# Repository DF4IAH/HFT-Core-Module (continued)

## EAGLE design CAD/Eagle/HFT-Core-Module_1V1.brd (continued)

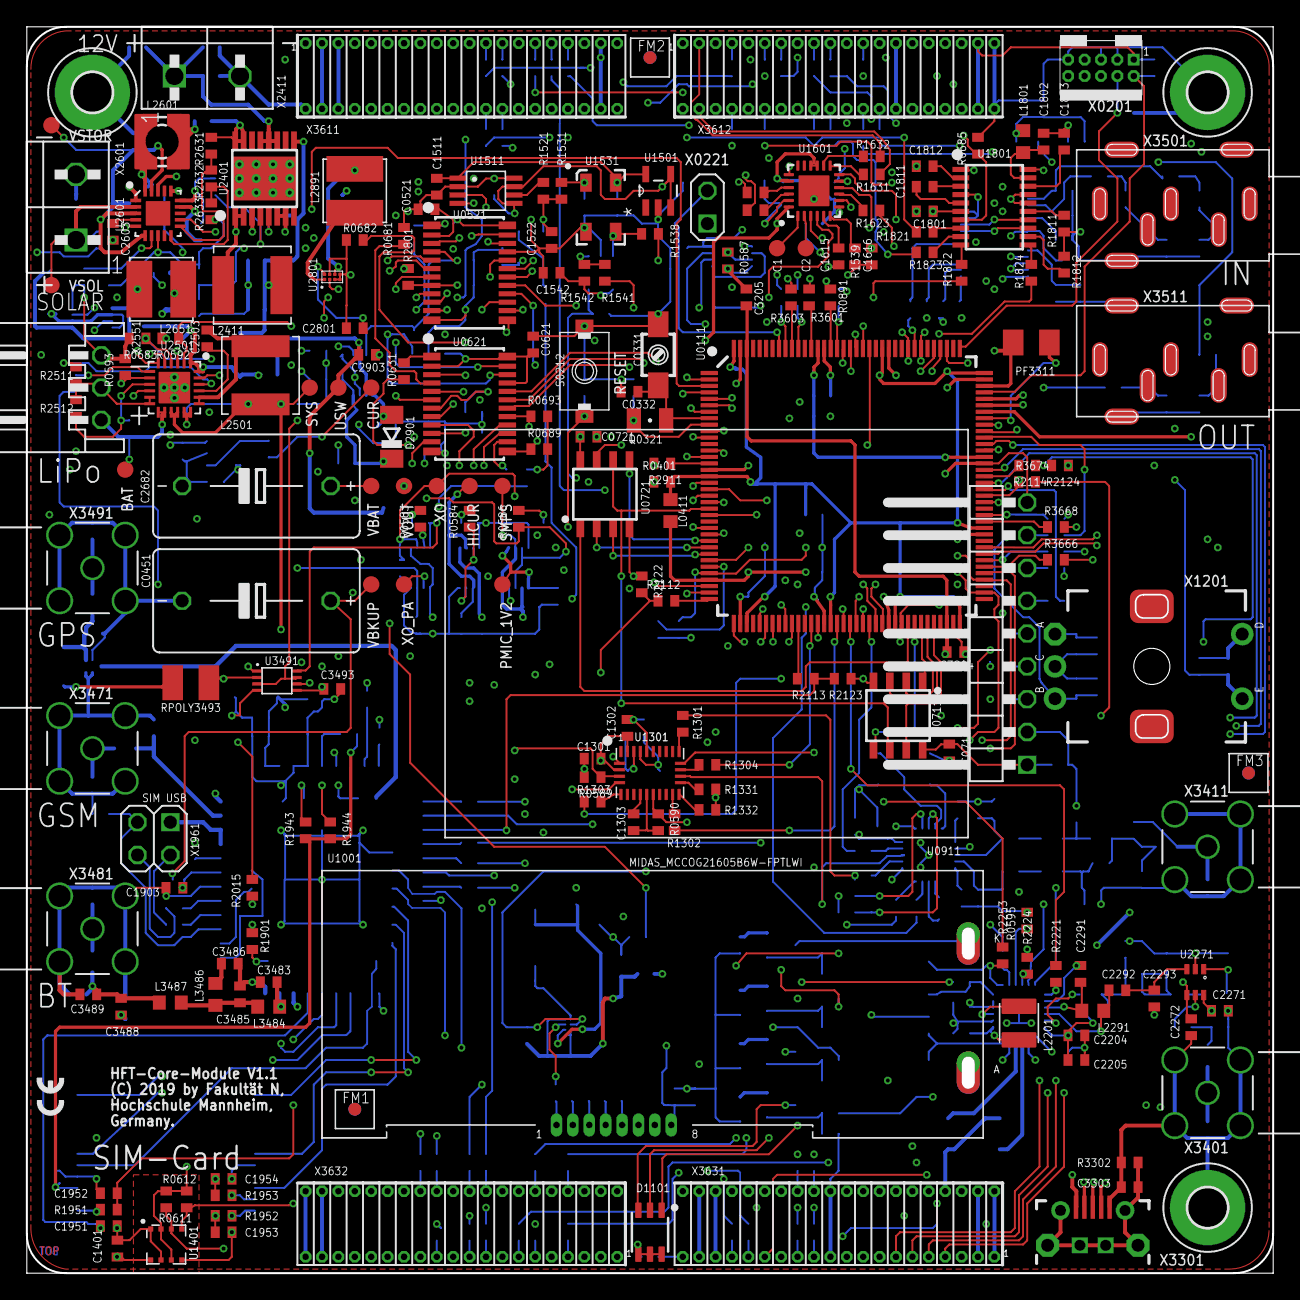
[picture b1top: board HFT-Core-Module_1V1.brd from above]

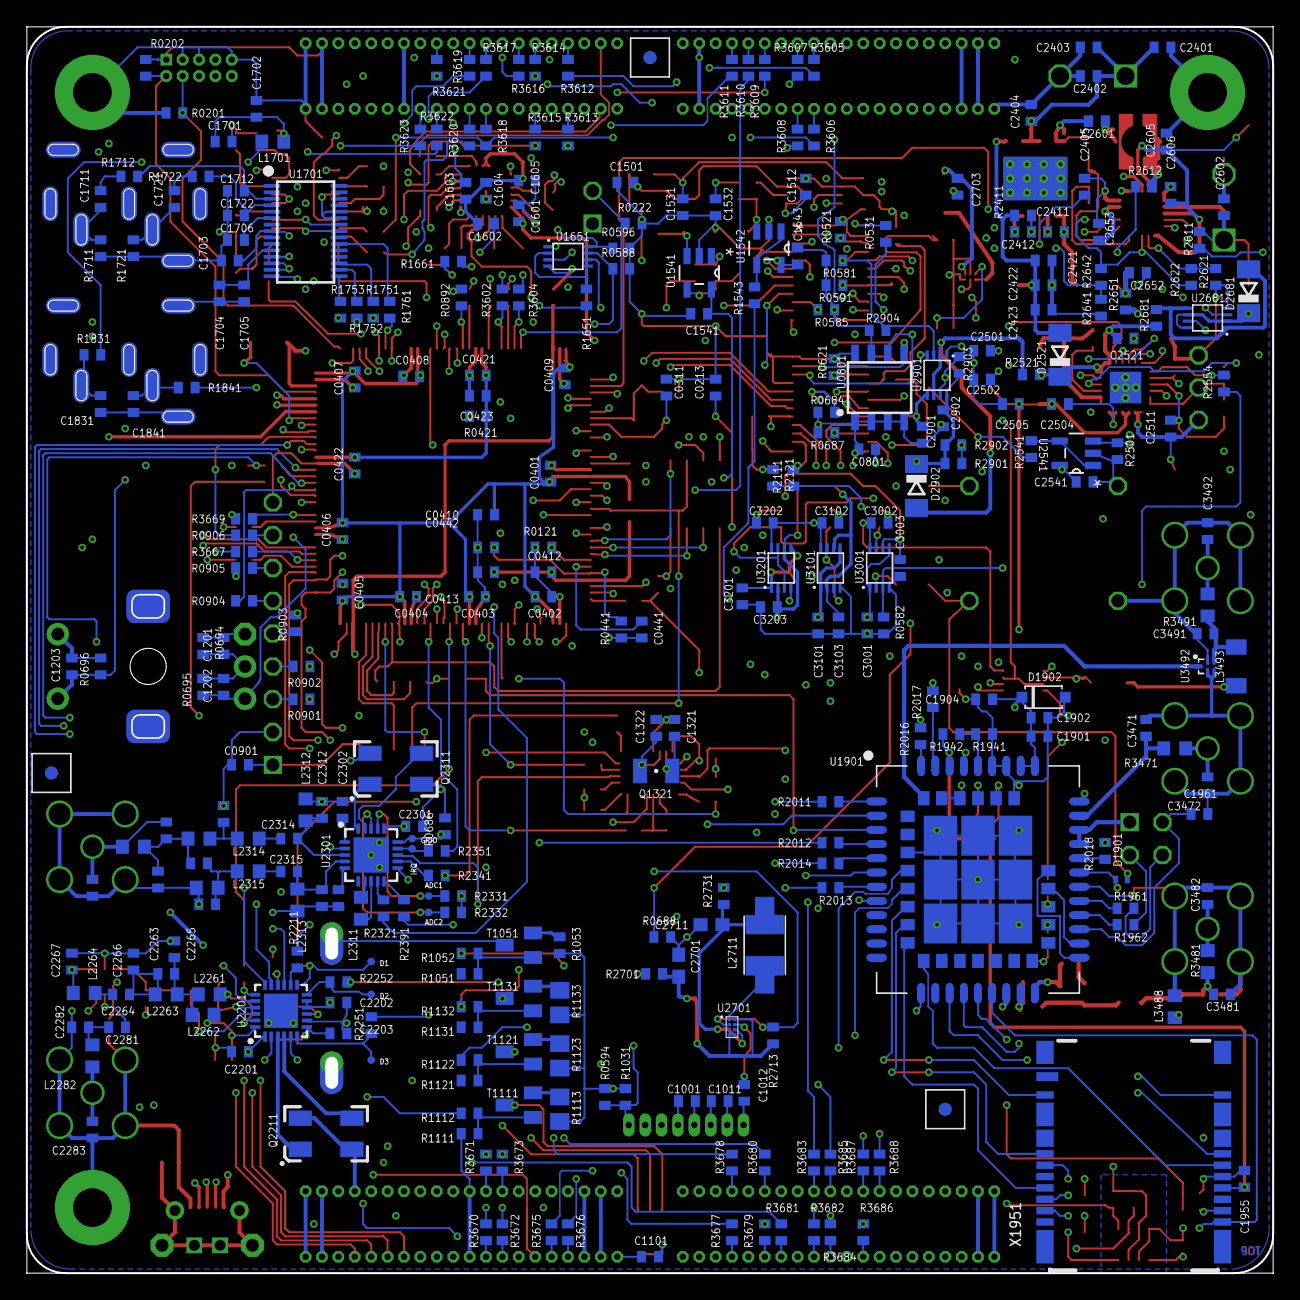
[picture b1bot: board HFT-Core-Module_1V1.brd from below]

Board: 6 copper layers, 96.5 x 96.5 mm, 518 parts (320 on the bottom side), 412 nets.

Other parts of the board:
FM1, FM2, FM3: FIDUCIAL_MARK_1MM

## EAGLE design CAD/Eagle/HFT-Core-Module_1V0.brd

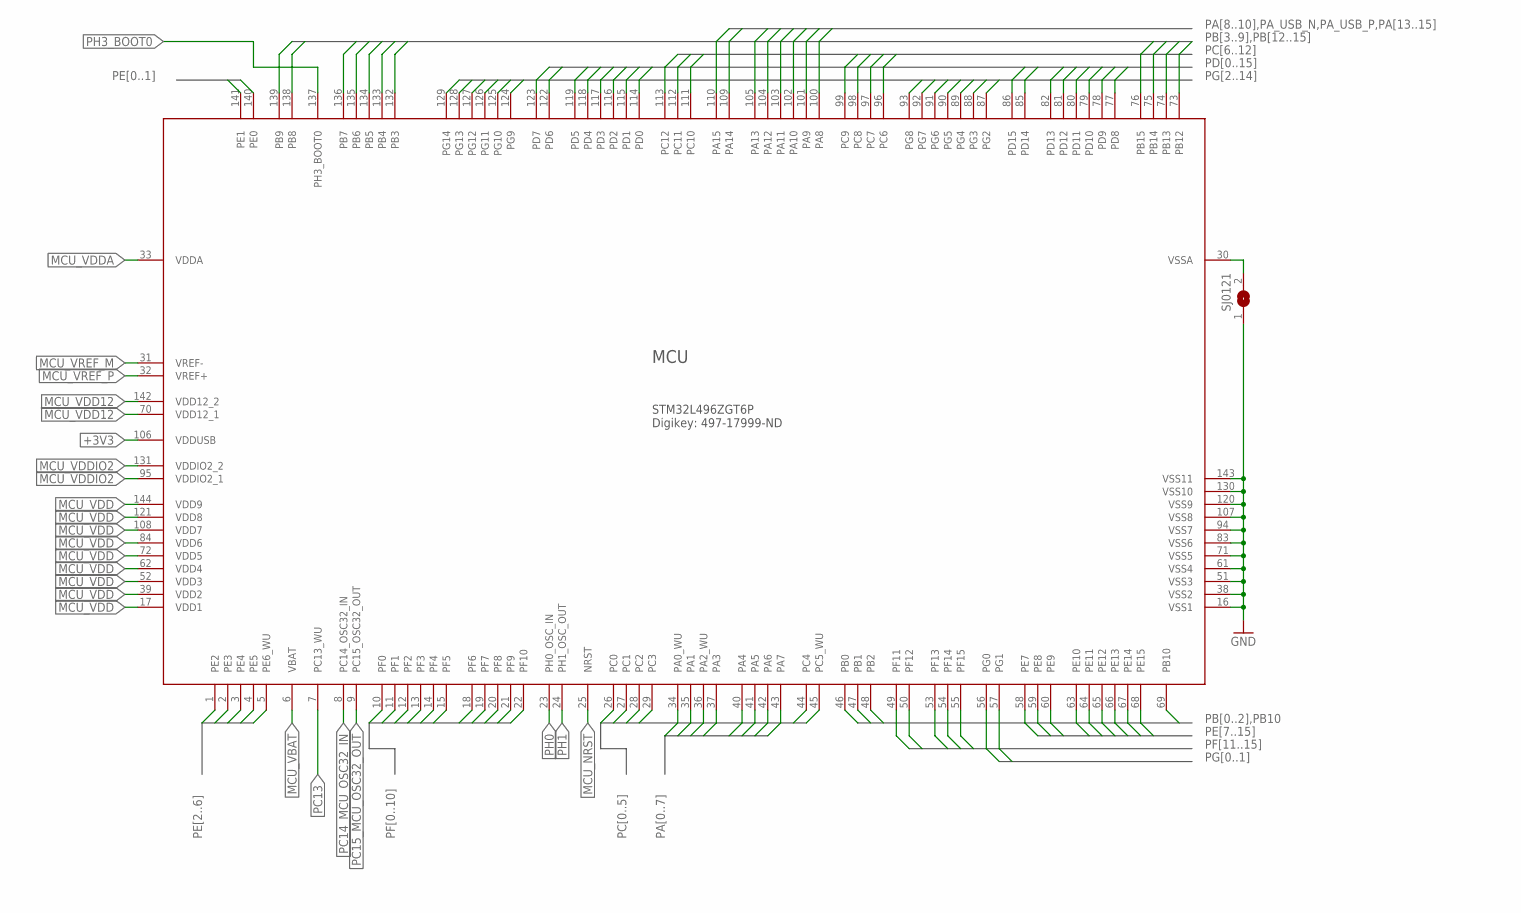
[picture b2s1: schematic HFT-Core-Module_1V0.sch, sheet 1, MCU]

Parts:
SJ0121: SJ
U0111: STM32L4Z_144PIN_SMPS; LQFP144

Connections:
+3V3: U0111.106 (VDDUSB); also elsewhere on the board
GND: SJ0121.1, U0111.16 (VSS1), U0111.38 (VSS2), U0111.51 (VSS3), U0111.61 (VSS4), U0111.71 (VSS5), U0111.83 (VSS6), U0111.94 (VSS7), U0111.107 (VSS8), U0111.120 (VSS9), U0111.130 (VSS10), U0111.143 (VSS11); also elsewhere on the board
MCU_NRST: U0111.25 (NRST); also elsewhere on the board
MCU_VBAT: U0111.6 (VBAT); also elsewhere on the board
MCU_VDD: U0111.17 (VDD1), U0111.39 (VDD2), U0111.52 (VDD3), U0111.62 (VDD4), U0111.72 (VDD5), U0111.84 (VDD6), U0111.108 (VDD7), U0111.121 (VDD8), U0111.144 (VDD9); also elsewhere on the board
MCU_VDD12: U0111.70 (VDD12_1), U0111.142 (VDD12_2); also elsewhere on the board
MCU_VDDA: U0111.33 (VDDA); also elsewhere on the board
MCU_VDDIO2: U0111.95 (VDDIO2_1), U0111.131 (VDDIO2_2); also elsewhere on the board
MCU_VREF_M: U0111.31 (VREF-); also elsewhere on the board
MCU_VREF_P: U0111.32 (VREF+); also elsewhere on the board
MCU_VSSA: SJ0121.2, U0111.30 (VSSA)
PA0: U0111.34 (PA0_WU); also elsewhere on the board
PA1: U0111.35 (PA1)
PA2: U0111.36 (PA2_WU); also elsewhere on the board
PA3: U0111.37 (PA3); also elsewhere on the board
PA4: U0111.40 (PA4)
PA5: U0111.41 (PA5)
PA6: U0111.42 (PA6); also elsewhere on the board
PA7: U0111.43 (PA7); also elsewhere on the board
PA8: U0111.100 (PA8); also elsewhere on the board
PA9: U0111.101 (PA9); also elsewhere on the board
PA10: U0111.102 (PA10); also elsewhere on the board
PA13: U0111.105 (PA13); also elsewhere on the board
PA14: U0111.109 (PA14); also elsewhere on the board
PA15: U0111.110 (PA15)
PA_USB_N: U0111.103 (PA11); also elsewhere on the board
PA_USB_P: U0111.104 (PA12); also elsewhere on the board
PB0: U0111.46 (PB0); also elsewhere on the board
PB1: U0111.47 (PB1); also elsewhere on the board
PB2: U0111.48 (PB2)
PB3: U0111.132 (PB3); also elsewhere on the board
PB4: U0111.133 (PB4)
PB5: U0111.134 (PB5); also elsewhere on the board
PB6: U0111.135 (PB6); also elsewhere on the board
PB7: U0111.136 (PB7); also elsewhere on the board
PB8: U0111.138 (PB8)
PB9: U0111.139 (PB9)
PB10: U0111.69 (PB10); also elsewhere on the board
PB12: U0111.73 (PB12); also elsewhere on the board
PB13: U0111.74 (PB13); also elsewhere on the board
PB14: U0111.75 (PB14); also elsewhere on the board
PB15: U0111.76 (PB15)
PC0: U0111.26 (PC0); also elsewhere on the board
PC1: U0111.27 (PC1); also elsewhere on the board
PC2: U0111.28 (PC2); also elsewhere on the board
PC3: U0111.29 (PC3); also elsewhere on the board
PC4: U0111.44 (PC4); also elsewhere on the board
PC5: U0111.45 (PC5_WU); also elsewhere on the board
PC6: U0111.96 (PC6); also elsewhere on the board
PC7: U0111.97 (PC7)
PC8: U0111.98 (PC8); also elsewhere on the board
PC9: U0111.99 (PC9); also elsewhere on the board
PC10: U0111.111 (PC10); also elsewhere on the board
PC11: U0111.112 (PC11); also elsewhere on the board
PC12: U0111.113 (PC12); also elsewhere on the board
PC13: U0111.7 (PC13_WU); also elsewhere on the board
PC14_MCU_OSC32_IN: U0111.8 (PC14_OSC32_IN); also elsewhere on the board
PC15_MCU_OSC32_OUT: U0111.9 (PC15_OSC32_OUT); also elsewhere on the board
PD0: U0111.114 (PD0); also elsewhere on the board
PD1: U0111.115 (PD1); also elsewhere on the board
PD2: U0111.116 (PD2); also elsewhere on the board
PD3: U0111.117 (PD3); also elsewhere on the board
PD4: U0111.118 (PD4); also elsewhere on the board
PD5: U0111.119 (PD5); also elsewhere on the board
PD6: U0111.122 (PD6); also elsewhere on the board
PD7: U0111.123 (PD7); also elsewhere on the board
PD8: U0111.77 (PD8); also elsewhere on the board
PD9: U0111.78 (PD9); also elsewhere on the board
PD10: U0111.79 (PD10); also elsewhere on the board
PD11: U0111.80 (PD11); also elsewhere on the board
PD12: U0111.81 (PD12); also elsewhere on the board
PD13: U0111.82 (PD13); also elsewhere on the board
PD14: U0111.85 (PD14); also elsewhere on the board
PD15: U0111.86 (PD15); also elsewhere on the board
PE0: U0111.140 (PE0); also elsewhere on the board
PE1: U0111.141 (PE1)
PE2: U0111.1 (PE2); also elsewhere on the board
PE3: U0111.2 (PE3); also elsewhere on the board
PE4: U0111.3 (PE4); also elsewhere on the board
PE5: U0111.4 (PE5); also elsewhere on the board
PE6: U0111.5 (PE6_WU)
PE7: U0111.58 (PE7); also elsewhere on the board
PE8: U0111.59 (PE8); also elsewhere on the board
PE9: U0111.60 (PE9); also elsewhere on the board
PE10: U0111.63 (PE10); also elsewhere on the board
PE11: U0111.64 (PE11); also elsewhere on the board
PE12: U0111.65 (PE12); also elsewhere on the board
PE13: U0111.66 (PE13); also elsewhere on the board
PE14: U0111.67 (PE14); also elsewhere on the board
PE15: U0111.68 (PE15); also elsewhere on the board
PF0: U0111.10 (PF0); also elsewhere on the board
PF1: U0111.11 (PF1); also elsewhere on the board
PF2: U0111.12 (PF2); also elsewhere on the board
PF3: U0111.13 (PF3); also elsewhere on the board
PF4: U0111.14 (PF4)
PF5: U0111.15 (PF5)
PF6: U0111.18 (PF6); also elsewhere on the board
PF7: U0111.19 (PF7); also elsewhere on the board
PF8: U0111.20 (PF8); also elsewhere on the board
PF9: U0111.21 (PF9); also elsewhere on the board
PF10: U0111.22 (PF10); also elsewhere on the board
PF11: U0111.49 (PF11)
PF12: U0111.50 (PF12); also elsewhere on the board
PF13: U0111.53 (PF13); also elsewhere on the board
PF14: U0111.54 (PF14); also elsewhere on the board
PF15: U0111.55 (PF15)
PG0: U0111.56 (PG0); also elsewhere on the board
PG1: U0111.57 (PG1); also elsewhere on the board
PG2: U0111.87 (PG2); also elsewhere on the board
PG3: U0111.88 (PG3); also elsewhere on the board
PG4: U0111.89 (PG4); also elsewhere on the board
PG5: U0111.90 (PG5)
PG6: U0111.91 (PG6)
PG7: U0111.92 (PG7); also elsewhere on the board
PG8: U0111.93 (PG8); also elsewhere on the board
PG9: U0111.124 (PG9); also elsewhere on the board
PG10: U0111.125 (PG10); also elsewhere on the board
PG11: U0111.126 (PG11); also elsewhere on the board
PG12: U0111.127 (PG12); also elsewhere on the board
PG13: U0111.128 (PG13); also elsewhere on the board
PG14: U0111.129 (PG14); also elsewhere on the board
PH0: U0111.23 (PH0_OSC_IN); also elsewhere on the board
PH1: U0111.24 (PH1_OSC_OUT)
PH3_BOOT0: U0111.137 (PH3_BOOT0); also elsewhere on the board

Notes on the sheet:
STM32L496ZGT6P Digikey: 497-17999-ND
MCU

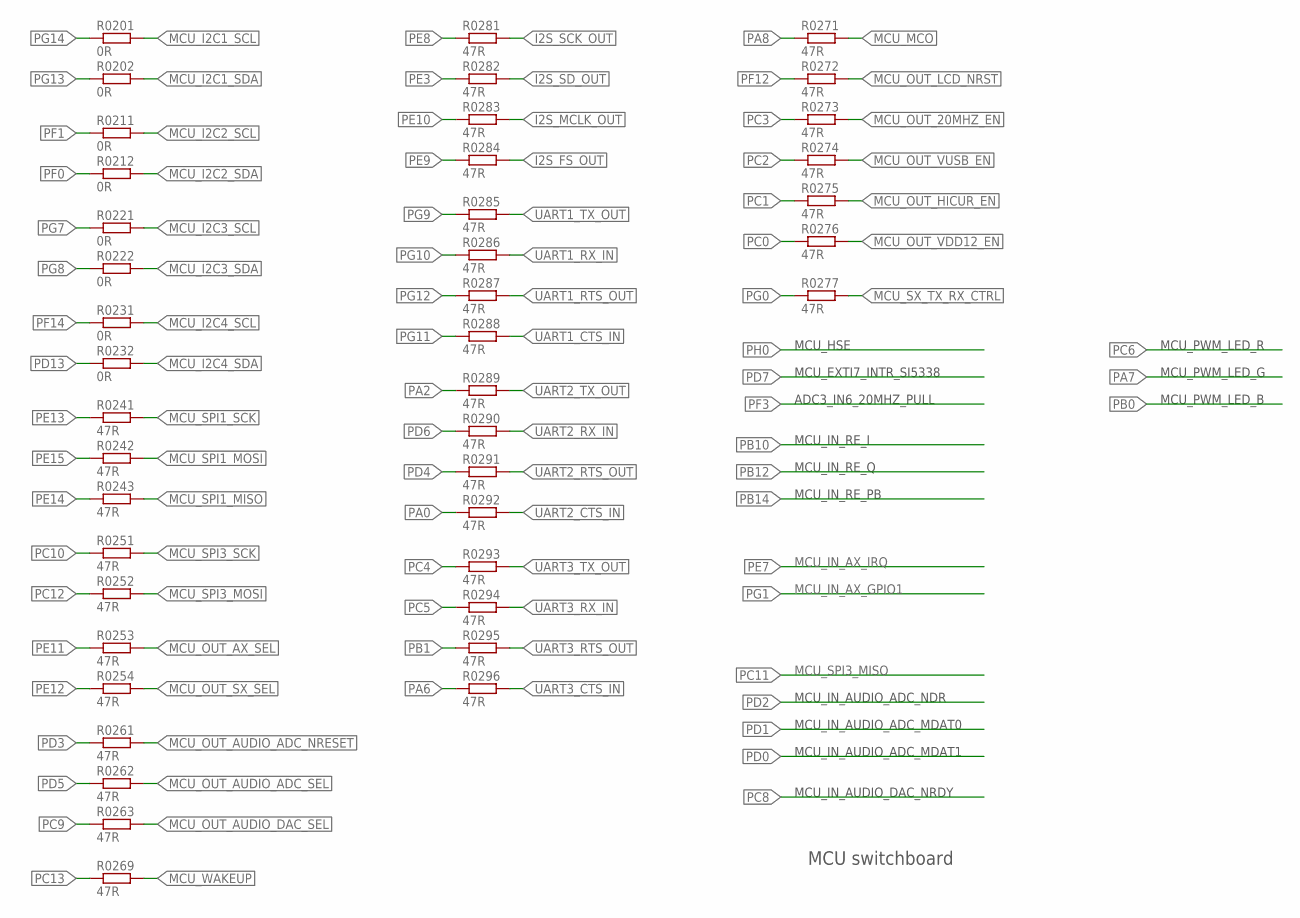
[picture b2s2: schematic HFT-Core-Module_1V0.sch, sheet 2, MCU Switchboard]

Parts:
R0201, R0202, R0211, R0212, R0221, R0222, R0231, R0232: 0R; R0603
R0241, R0242, R0243, R0251, R0252, R0253, R0254, R0261, R0262, R0263, R0269, R0271, R0272, R0273, R0274, R0275, R0276, R0277, R0281, R0282, R0283, R0284, R0285, R0286, R0287, R0288, R0289, R0290, R0291, R0292, R0293, R0294, R0295, R0296: 47R; R0603

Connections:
I2S_FS_OUT: R0284.2; also elsewhere on the board
I2S_MCLK_OUT: R0283.2; also elsewhere on the board
I2S_SCK_OUT: R0281.2; also elsewhere on the board
I2S_SD_OUT: R0282.2; also elsewhere on the board
MCU_I2C1_SCL: R0201.2; also elsewhere on the board
MCU_I2C1_SDA: R0202.2; also elsewhere on the board
MCU_I2C2_SCL: R0211.2; also elsewhere on the board
MCU_I2C2_SDA: R0212.2; also elsewhere on the board
MCU_I2C3_SCL: R0221.2; also elsewhere on the board
MCU_I2C3_SDA: R0222.2; also elsewhere on the board
MCU_I2C4_SCL: R0231.2; also elsewhere on the board
MCU_I2C4_SDA: R0232.2; also elsewhere on the board
MCU_MCO: R0271.2; also elsewhere on the board
MCU_OUT_20MHZ_EN: R0273.2; also elsewhere on the board
MCU_OUT_AUDIO_ADC_NRESET: R0261.2; also elsewhere on the board
MCU_OUT_AUDIO_ADC_SEL: R0262.2; also elsewhere on the board
MCU_OUT_AUDIO_DAC_SEL: R0263.2; also elsewhere on the board
MCU_OUT_AX_SEL: R0253.2; also elsewhere on the board
MCU_OUT_HICUR_EN: R0275.2; also elsewhere on the board
MCU_OUT_LCD_NRST: R0272.2; also elsewhere on the board
MCU_OUT_SX_SEL: R0254.2; also elsewhere on the board
MCU_OUT_VDD12_EN: R0276.2; also elsewhere on the board
MCU_OUT_VUSB_EN: R0274.2; also elsewhere on the board
MCU_SPI1_MISO: R0243.2; also elsewhere on the board
MCU_SPI1_MOSI: R0242.2; also elsewhere on the board
MCU_SPI1_SCK: R0241.2; also elsewhere on the board
MCU_SPI3_MOSI: R0252.2; also elsewhere on the board
MCU_SPI3_SCK: R0251.2; also elsewhere on the board
MCU_SX_TX_RX_CTRL: R0277.2; also elsewhere on the board
MCU_WAKEUP: R0269.2; also elsewhere on the board
PA0: R0292.1; also elsewhere on the board
PA2: R0289.1; also elsewhere on the board
PA6: R0296.1; also elsewhere on the board
PA8: R0271.1; also elsewhere on the board
PB1: R0295.1; also elsewhere on the board
PC0: R0276.1; also elsewhere on the board
PC1: R0275.1; also elsewhere on the board
PC2: R0274.1; also elsewhere on the board
PC3: R0273.1; also elsewhere on the board
PC4: R0293.1; also elsewhere on the board
PC5: R0294.1; also elsewhere on the board
PC9: R0263.1; also elsewhere on the board
PC10: R0251.1; also elsewhere on the board
PC12: R0252.1; also elsewhere on the board
PC13: R0269.1; also elsewhere on the board
PD3: R0261.1; also elsewhere on the board
PD4: R0291.1; also elsewhere on the board
PD5: R0262.1; also elsewhere on the board
PD6: R0290.1; also elsewhere on the board
PD13: R0232.1; also elsewhere on the board
PE3: R0282.1; also elsewhere on the board
PE8: R0281.1; also elsewhere on the board
PE9: R0284.1; also elsewhere on the board
PE10: R0283.1; also elsewhere on the board
PE11: R0253.1; also elsewhere on the board
PE12: R0254.1; also elsewhere on the board
PE13: R0241.1; also elsewhere on the board
PE14: R0243.1; also elsewhere on the board
PE15: R0242.1; also elsewhere on the board
PF0: R0212.1; also elsewhere on the board
PF1: R0211.1; also elsewhere on the board
PF12: R0272.1; also elsewhere on the board
PF14: R0231.1; also elsewhere on the board
PG0: R0277.1; also elsewhere on the board
PG7: R0221.1; also elsewhere on the board
PG8: R0222.1; also elsewhere on the board
PG9: R0285.1; also elsewhere on the board
PG10: R0286.1; also elsewhere on the board
PG11: R0288.1; also elsewhere on the board
PG12: R0287.1; also elsewhere on the board
PG13: R0202.1; also elsewhere on the board
PG14: R0201.1; also elsewhere on the board
UART1_CTS_IN: R0288.2; also elsewhere on the board
UART1_RTS_OUT: R0287.2; also elsewhere on the board
UART1_RX_IN: R0286.2; also elsewhere on the board
UART1_TX_OUT: R0285.2; also elsewhere on the board
UART2_CTS_IN: R0292.2; also elsewhere on the board
UART2_RTS_OUT: R0291.2; also elsewhere on the board
UART2_RX_IN: R0290.2; also elsewhere on the board
UART2_TX_OUT: R0289.2; also elsewhere on the board
UART3_CTS_IN: R0296.2; also elsewhere on the board
UART3_RTS_OUT: R0295.2; also elsewhere on the board
UART3_RX_IN: R0294.2; also elsewhere on the board
UART3_TX_OUT: R0293.2; also elsewhere on the board

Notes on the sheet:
MCU_SPI3_MISO
MCU_IN_AX_IRQ
MCU_IN_AX_GPIO1
MCU switchboard
MCU_IN_AUDIO_ADC_NDR
MCU_IN_AUDIO_ADC_MDAT0
MCU_IN_AUDIO_ADC_MDAT1
MCU_IN_RE_I
MCU_IN_RE_Q
MCU_IN_RE_PB
ADC3_IN6_20MHZ_PULL
MCU_HSE
MCU_EXTI7_INTR_SI5338
MCU_IN_AUDIO_DAC_NRDY
MCU_PWM_LED_R
MCU_PWM_LED_G
MCU_PWM_LED_B

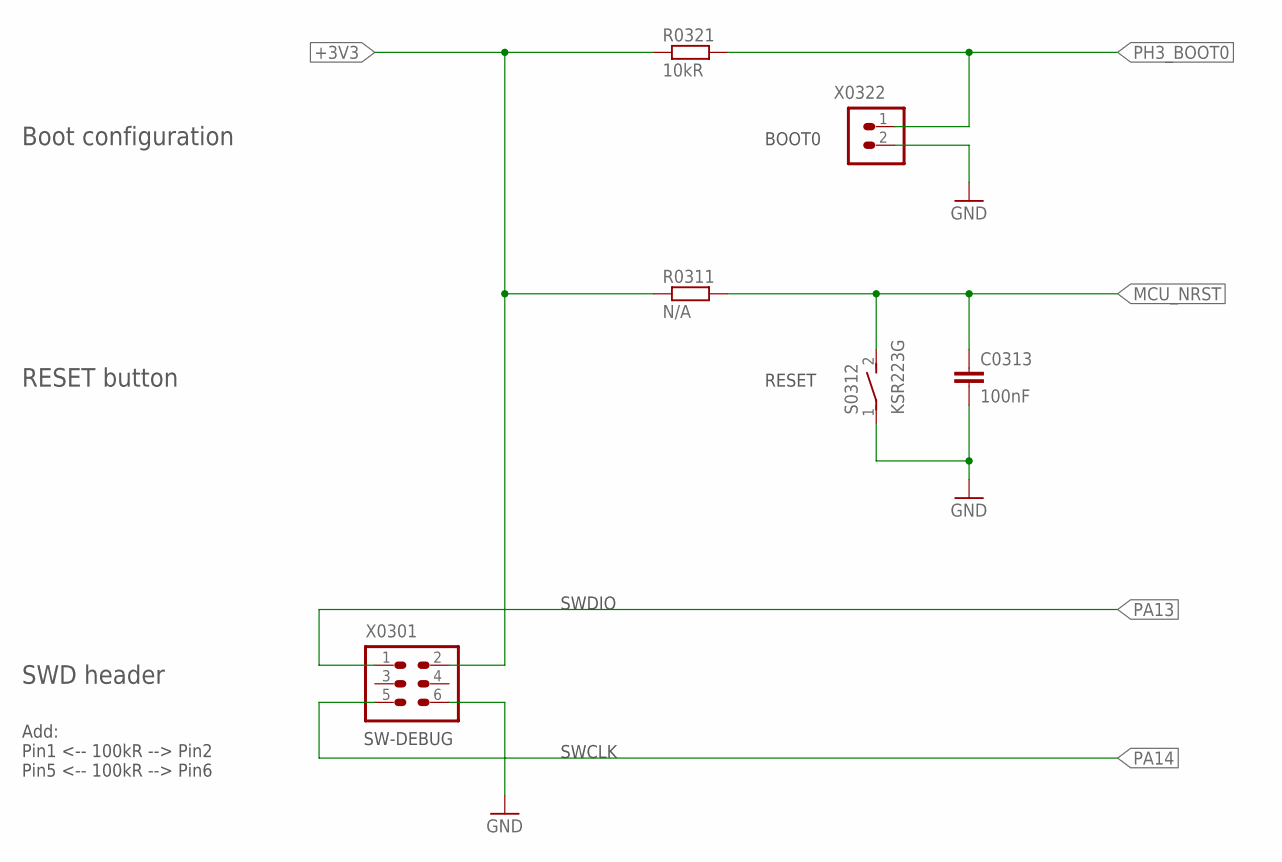
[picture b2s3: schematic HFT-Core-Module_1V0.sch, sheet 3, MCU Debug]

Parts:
C0313: 100nF; C0603
R0311: N/A; R0603
R0321: 10kR; R0603
S0312: KSR223G; KSR223G_SMD_1POL
X0301: HEADER-2X3; 2X03
X0322: HEADER-1X2; 1X02

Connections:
+3V3: R0311.1, R0321.1, X0301.2; also elsewhere on the board
GND: C0313.2, S0312.1, X0301.6, X0322.2; also elsewhere on the board
MCU_NRST: C0313.1, R0311.2, S0312.2 (S); also elsewhere on the board
PA13: X0301.1; also elsewhere on the board
PA14: X0301.5; also elsewhere on the board
PH3_BOOT0: R0321.2, X0322.1; also elsewhere on the board

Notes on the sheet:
SWDIO
SWCLK
RESET
BOOT0
SW-DEBUG
SWD header
Boot configuration
RESET button
Add: Pin1 <-- 100kR --> Pin2 Pin5 <-- 100kR --> Pin6

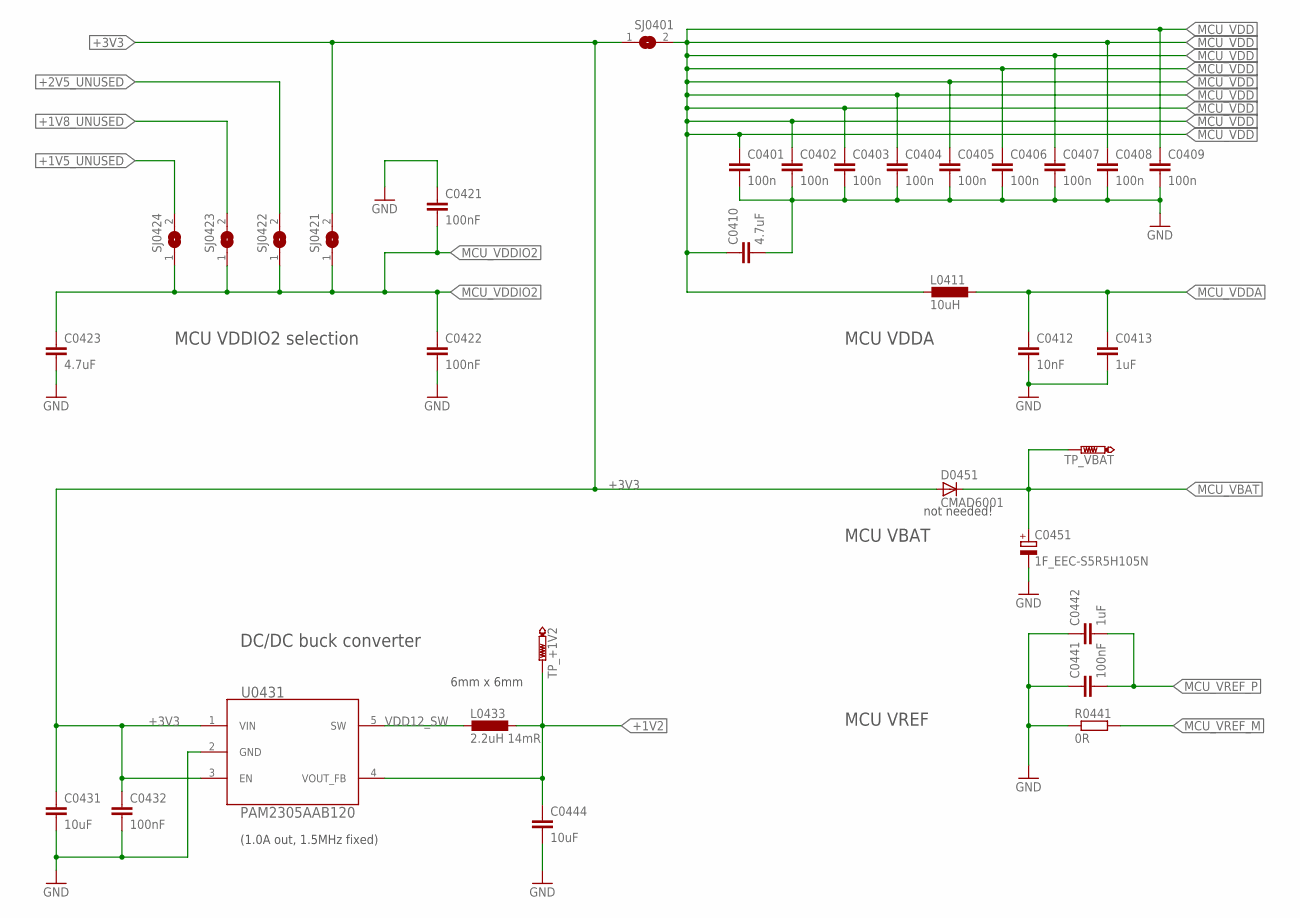
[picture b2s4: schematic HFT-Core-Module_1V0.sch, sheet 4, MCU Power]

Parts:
C0401, C0402, C0403, C0404, C0405, C0406, C0407, C0408, C0409: 100n; C0603
C0410, C0423: 4.7uF; C0805
C0412: 10nF; C0603
C0413, C0442: 1uF; C0805
C0421, C0422, C0432, C0441: 100nF; C0603
C0431, C0444: 10uF; C0805
C0451: 1F_EEC-S5R5H105N; W14MM_D8MM_P13MM5
D0451: CMAD6001; SOD923
L0411: 10uH; L2012C
L0433: 2.2uH 14mR; L_6X6MM
R0441: 0R; R0603
SJ0401, SJ0421, SJ0422, SJ0423, SJ0424: SJ
TP_+1V2: PTR1B1,27; B1,27
TP_VBAT: PTR1B1,27; B1,27
U0431: PAM2305AAB120; SOT95P280X145-5N

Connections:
+1V2: C0444.1, L0433.1, TP_+1V2.TP, U0431.4 (VOUT_FB); also elsewhere on the board
+1V5_UNUSED: SJ0424.2
+1V8_UNUSED: SJ0423.2
+2V5_UNUSED: SJ0422.2
+3V3: C0431.1, C0432.1, D0451.A, SJ0401.1, SJ0421.2, U0431.1 (VIN), U0431.3 (EN); also elsewhere on the board
GND: C0401.2, C0402.2, C0403.2, C0404.2, C0405.2, C0406.2, C0407.2, C0408.2, C0409.2, C0410.2, C0412.2, C0413.2, C0421.1, C0422.2, C0423.2, C0431.2, C0432.2, C0441.1, C0442.1, C0444.2, C0451.-, R0441.1, U0431.2 (GND); also elsewhere on the board
MCU_VBAT: C0451.+, D0451.C, TP_VBAT.TP; also elsewhere on the board
MCU_VDD: C0401.1, C0402.1, C0403.1, C0404.1, C0405.1, C0406.1, C0407.1, C0408.1, C0409.1, C0410.1, L0411.2, SJ0401.2; also elsewhere on the board
MCU_VDDA: C0412.1, C0413.1, L0411.1; also elsewhere on the board
MCU_VDDIO2: C0421.2, C0422.1, C0423.1, SJ0421.1, SJ0422.1, SJ0423.1, SJ0424.1; also elsewhere on the board
MCU_VREF_M: R0441.2; also elsewhere on the board
MCU_VREF_P: C0441.2, C0442.2; also elsewhere on the board
VDD12_SW: L0433.2, U0431.5 (SW)

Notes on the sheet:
6mm x 6mm
MCU VDDIO2 selection
MCU VDDA
DC/DC buck converter
MCU VREF
MCU VBAT
not needed!
(1.0A out, 1.5MHz fixed)

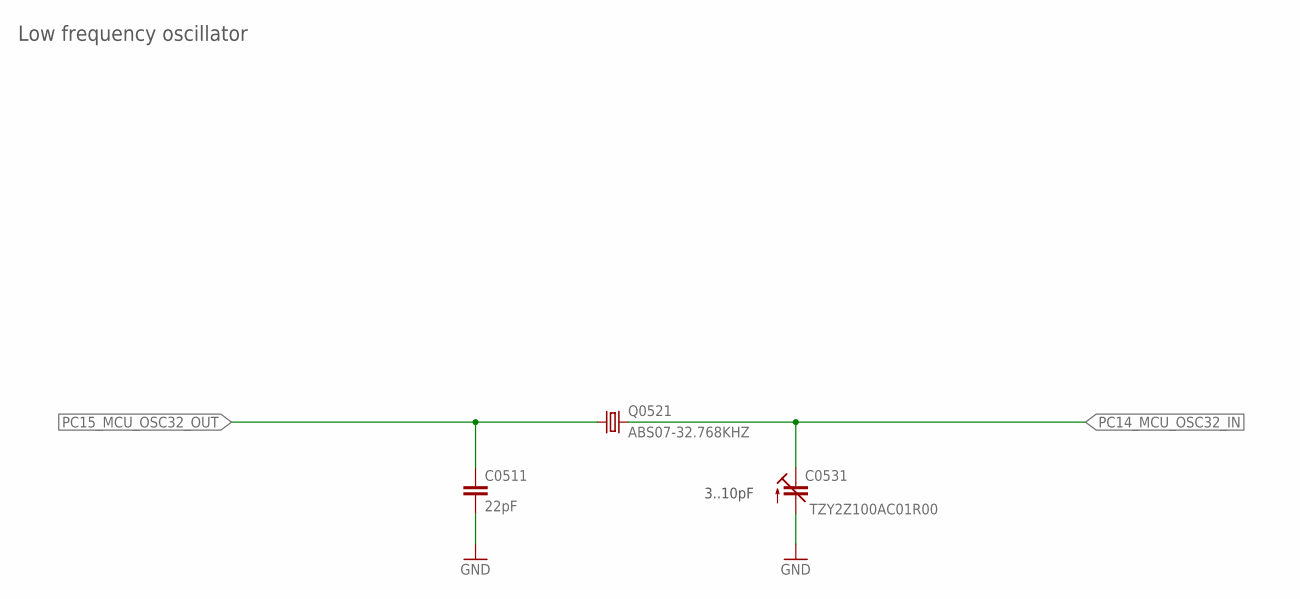
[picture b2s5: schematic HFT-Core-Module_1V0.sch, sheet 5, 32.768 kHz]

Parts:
C0511: 22pF; C0603
C0531: TZY2Z100AC01R00; 3MM2_X_2MM5
Q0521: ABS07-32.768KHZ; ABS07

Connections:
GND: C0511.2, C0531.+ (A); also elsewhere on the board
PC14_MCU_OSC32_IN: C0531.- (E), Q0521.2; also elsewhere on the board
PC15_MCU_OSC32_OUT: C0511.1, Q0521.1; also elsewhere on the board

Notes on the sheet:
3..10pF
Low frequency oscillator

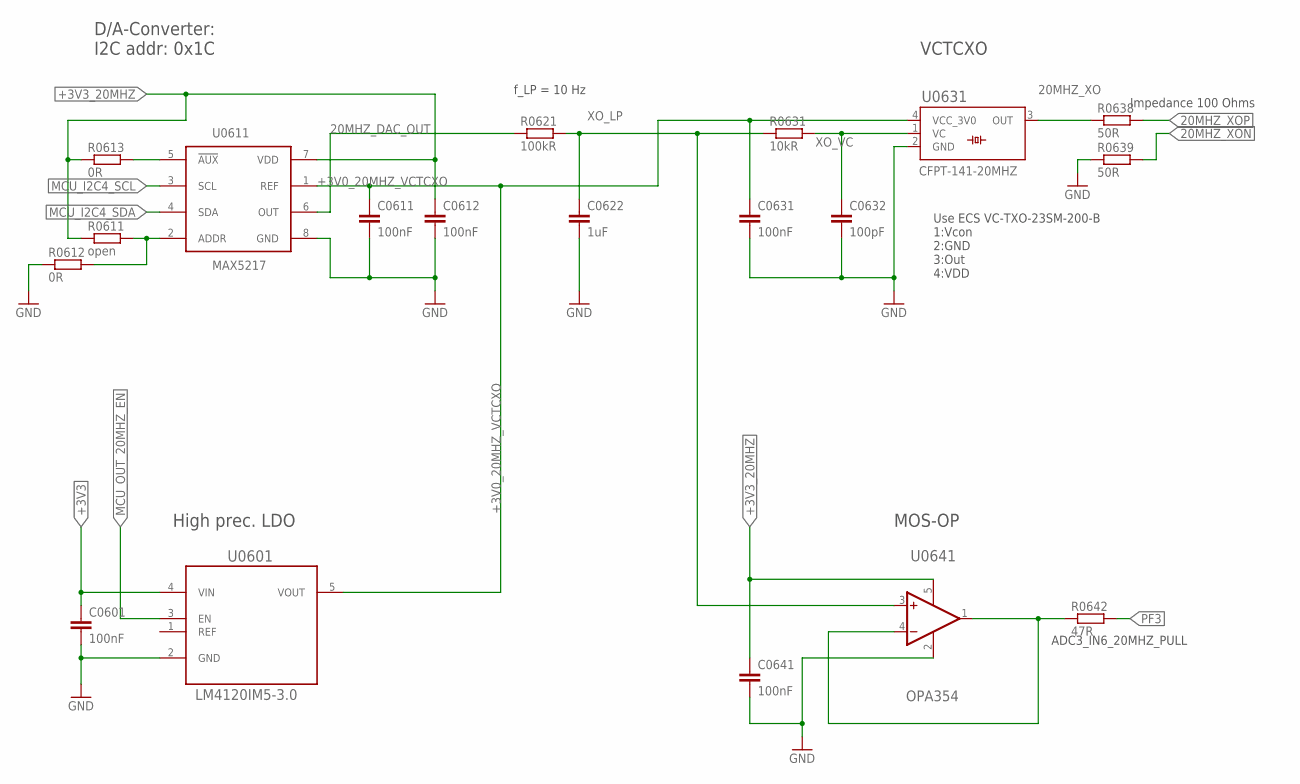
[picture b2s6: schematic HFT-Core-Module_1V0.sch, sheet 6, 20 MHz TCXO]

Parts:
C0601, C0611, C0612, C0631, C0641: 100nF; C0603
C0622: 1uF; C0805
C0632: 100pF; C0603
R0611: open; R0603
R0612, R0613: 0R; R0603
R0621: 100kR; R0603
R0631: 10kR; R0603
R0638, R0639: 50R; R0603
R0642: 47R; R0603
U0601: LM4120IM5-3.0; SOT95P285X120-5N
U0611: MAX5217; µMAX8
U0631: CFPT-141-20MHZ; CFPT-141
U0641: OPA354; SOT-23-5

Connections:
20MHZ_DAC_OUT: R0621.1, U0611.6 (OUT)
20MHZ_XO: R0638.1, U0631.3 (OUT)
20MHZ_XON: R0639.2; also elsewhere on the board
20MHZ_XOP: R0638.2; also elsewhere on the board
+3V0_20MHZ_VCTCXO: C0611.1, C0631.1, U0601.5 (VOUT), U0611.1 (REF), U0631.4 (VCC_3V0)
+3V3: C0601.1, U0601.4 (VIN); also elsewhere on the board
+3V3_20MHZ: C0612.1, C0641.1, R0611.1, R0613.1, U0611.7 (VDD), U0641.5 (V+); also elsewhere on the board
AD_VCTCXO1: R0642.1, U0641.1 (OUT), U0641.4 (-IN)
GND: C0601.2, C0611.2, C0612.2, C0622.2, C0631.2, C0632.2, C0641.2, R0612.1, R0639.1, U0601.2 (GND), U0611.8 (GND), U0631.2 (GND), U0641.2 (V-); also elsewhere on the board
MAX5217_!AUX: R0613.2, U0611.5 (!AUX)
MAX5217_ADDR: R0611.2, R0612.2, U0611.2 (ADDR)
MCU_I2C4_SCL: U0611.3 (SCL); also elsewhere on the board
MCU_I2C4_SDA: U0611.4 (SDA); also elsewhere on the board
MCU_OUT_20MHZ_EN: U0601.3 (EN); also elsewhere on the board
PF3: R0642.2; also elsewhere on the board
XO_LP: C0622.1, R0621.2, R0631.1, U0641.3 (+IN)
XO_VC: C0632.1, R0631.2, U0631.1 (VC)

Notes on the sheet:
f_LP = 10 Hz
Use ECS VC-TXO-23SM-200-B 1:Vcon 2:GND 3:Out 4:VDD
Impedance 100 Ohms
High prec. LDO
MOS-OP
VCTCXO
D/A-Converter: I2C addr: 0x1C
ADC3_IN6_20MHZ_PULL

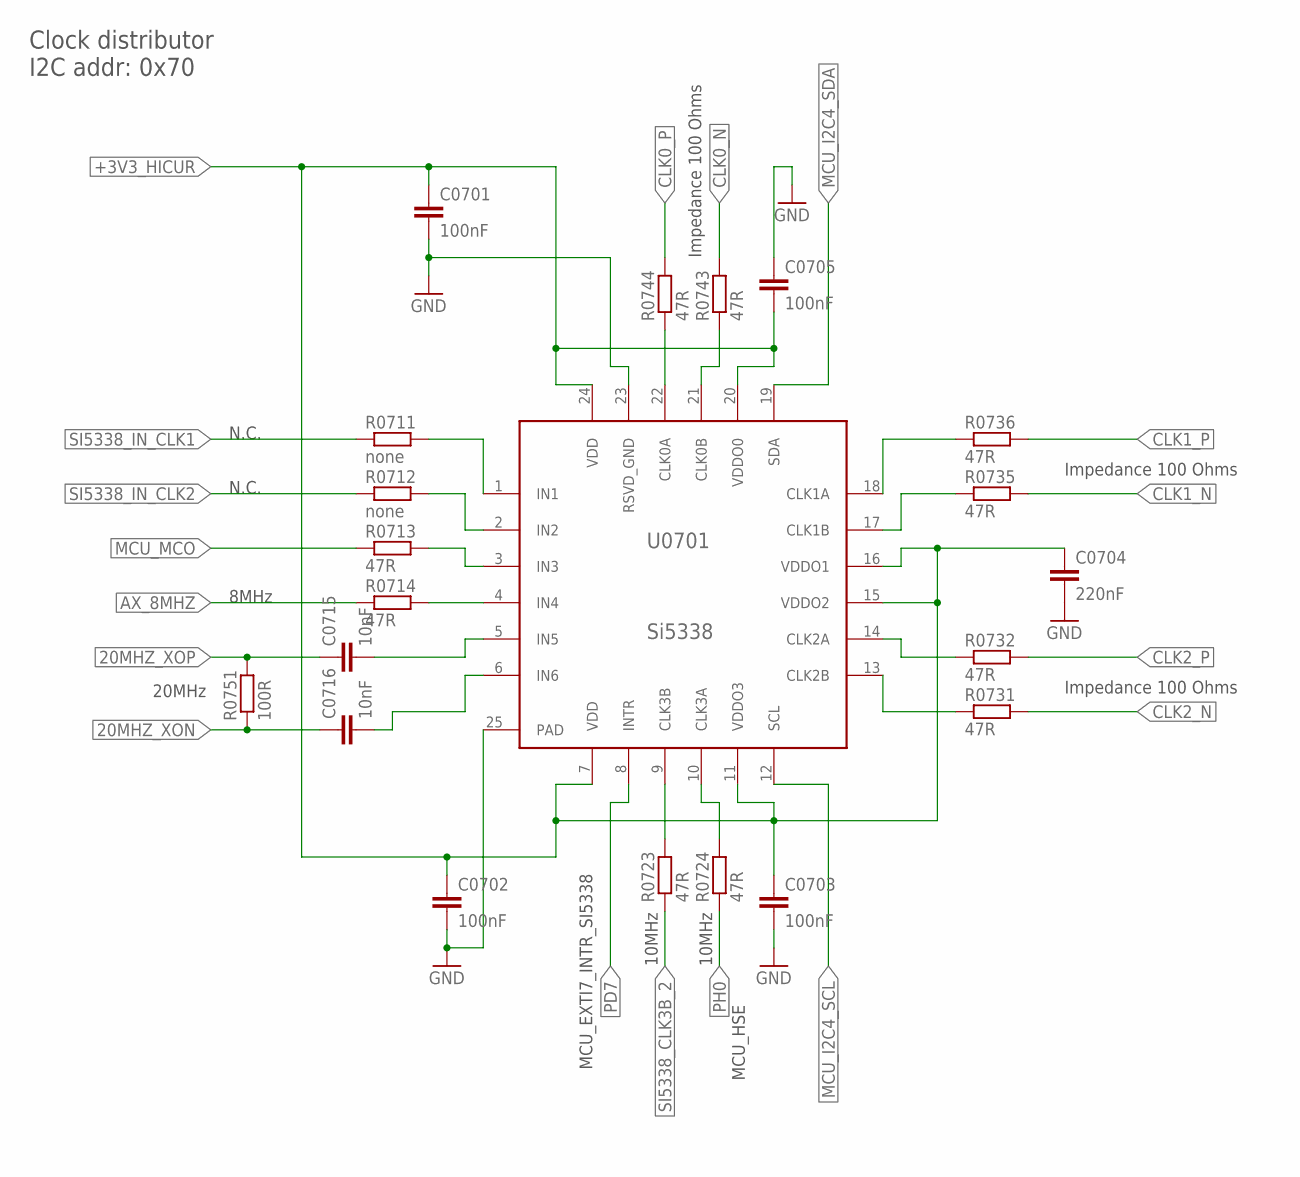
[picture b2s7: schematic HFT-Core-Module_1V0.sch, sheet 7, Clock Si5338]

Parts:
C0701, C0702, C0703, C0705: 100nF; C0603
C0704: 220nF; C0603
C0715, C0716: 10nF; C0603
R0711, R0712: none; R0603
R0713, R0714, R0723, R0724, R0731, R0732, R0735, R0736, R0743, R0744: 47R; R0603
R0751: 100R; R0603
U0701: Si5338; QFN24_P0MM5_CTRPAD

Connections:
20MHZ_XON: C0716.1, R0751.1; also elsewhere on the board
20MHZ_XOP: C0715.1, R0751.2; also elsewhere on the board
+3V3_HICUR: C0701.1, C0702.1, C0703.1, C0704.1, C0705.2, U0701.7 (VDD), U0701.11 (VDDO3), U0701.15 (VDDO2), U0701.16 (VDDO1), U0701.20 (VDDO0), U0701.24 (VDD); also elsewhere on the board
AX_8MHZ: R0714.1; also elsewhere on the board
CLK0_N: R0743.2; also elsewhere on the board
CLK0_P: R0744.2; also elsewhere on the board
CLK1_N: R0735.2; also elsewhere on the board
CLK1_P: R0736.2; also elsewhere on the board
CLK2_N: R0731.2; also elsewhere on the board
CLK2_P: R0732.2; also elsewhere on the board
GND: C0701.2, C0702.2, C0703.2, C0704.2, C0705.1, U0701.23 (RSVD_GND), U0701.25 (PAD); also elsewhere on the board
MCU_I2C4_SCL: U0701.12 (SCL); also elsewhere on the board
MCU_I2C4_SDA: U0701.19 (SDA); also elsewhere on the board
MCU_MCO: R0713.1; also elsewhere on the board
PD7: U0701.8 (INTR); also elsewhere on the board
PH0: R0724.1; also elsewhere on the board
SI5338_CLK0A: R0744.1, U0701.22 (CLK0A)
SI5338_CLK0B: R0743.1, U0701.21 (CLK0B)
SI5338_CLK1A: R0736.1, U0701.18 (CLK1A)
SI5338_CLK1B: R0735.1, U0701.17 (CLK1B)
SI5338_CLK2A: R0732.1, U0701.14 (CLK2A)
SI5338_CLK2B: R0731.1, U0701.13 (CLK2B)
SI5338_CLK3A: R0724.2, U0701.10 (CLK3A)
SI5338_CLK3B: R0723.2, U0701.9 (CLK3B)
SI5338_CLK3B_2: R0723.1; also elsewhere on the board
SI5338_IN1: R0711.2, U0701.1 (IN1)
SI5338_IN2: R0712.2, U0701.2 (IN2)
SI5338_IN3: R0713.2, U0701.3 (IN3)
SI5338_IN4: R0714.2, U0701.4 (IN4)
SI5338_IN5: C0715.2, U0701.5 (IN5)
SI5338_IN6: C0716.2, U0701.6 (IN6)
SI5338_IN_CLK1: R0711.1
SI5338_IN_CLK2: R0712.1

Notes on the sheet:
Impedance 100 Ohms
Clock distributor I2C addr: 0x70
10MHz
8MHz
20MHz
N.C.
MCU_EXTI7_INTR_SI5338
MCU_HSE
